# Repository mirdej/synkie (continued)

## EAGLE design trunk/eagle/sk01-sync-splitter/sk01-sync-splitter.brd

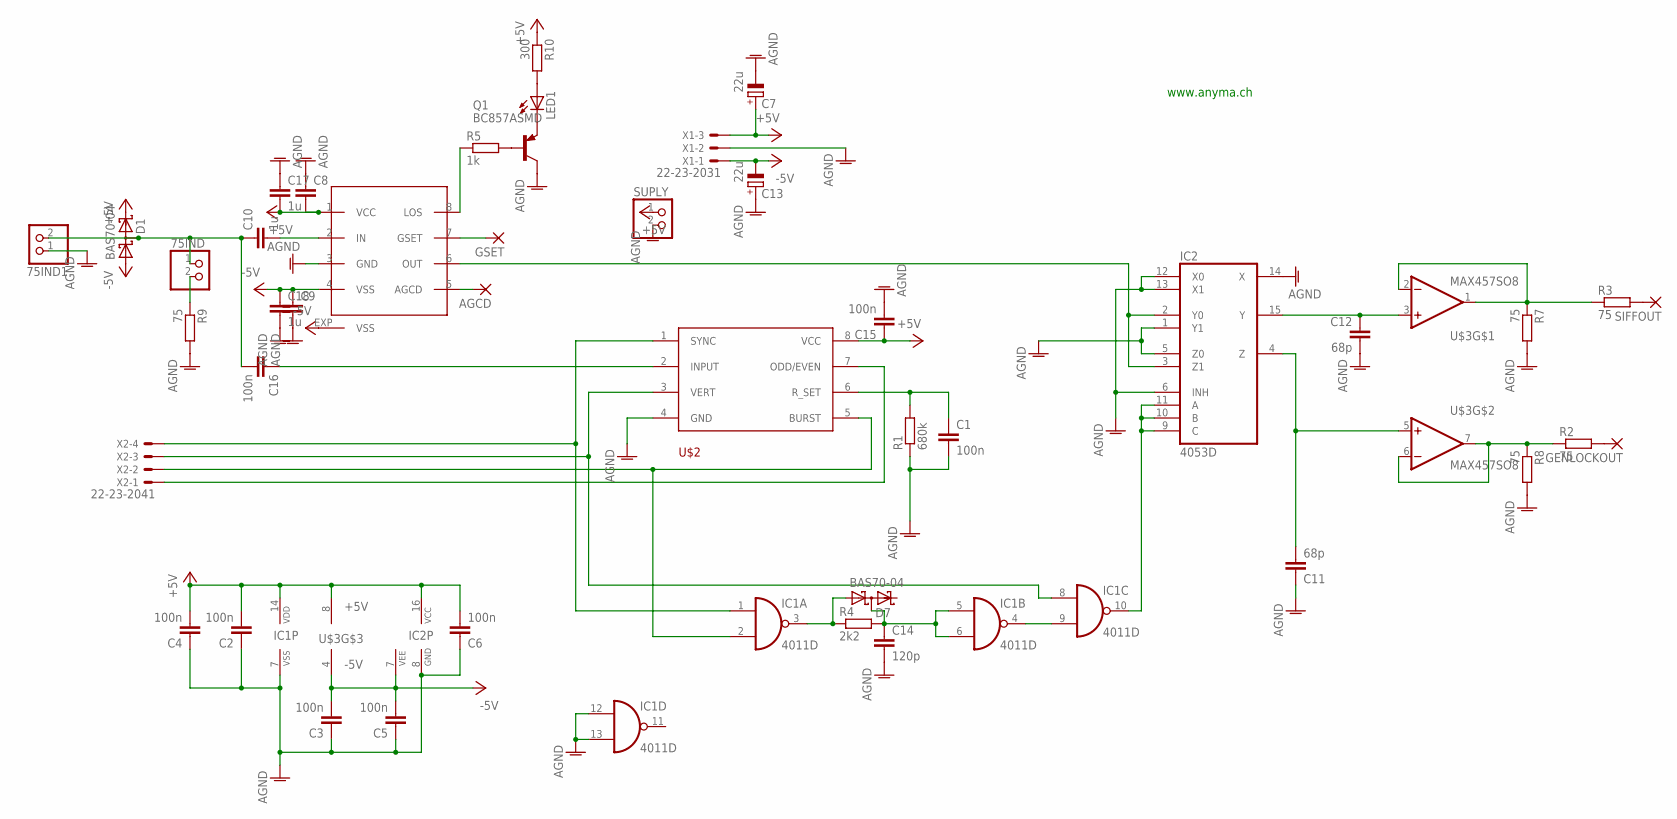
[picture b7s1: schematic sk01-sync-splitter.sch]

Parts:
75IND, 75IND1: PINHD-1X2; 1X02
AGCD: 3,17/1,1
C1, C2, C16: 100n; C1206
C3, C4, C5, C6, C15: 100n; C0805
C7, C13: 22u; CT3528
C8, C9: C-EUC0805; C0805
C10: 1u; C1206
C11, C12: 68p; C1206
C14: 120p; C1206
C17, C18: 1u; C0805
D1, D7: BAS70-04; SOT23
GENLOCKOUT: 3,17/1,1
GSET: 3,17/1,1
IC1: 4011D; SO14
IC2: 4053D; SO16
LED1: LED3MM
Q1: BC857ASMD; SOT23-BEC
R1: 680k; R1206
R2, R3, R7, R8, R9: 75; R1206
R4: 2k2; R1206
R5: 1k; R1206
R10: 300; R1206
SIFFOUT: 3,17/1,1
SUPLY: PINHD-1X2; 1X02
U$2: LM1881; SO08
U$3: MAX457SO8; SO08
U$4: MAX7450; SO08-EXP
X1: 22-23-2031
X2: 22-23-2041

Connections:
+5V: C2.2, C4.2, C6.2, C7.+, C8.2, C15.1, C17.2, D1.2 (C2), IC1.14 (VDD), IC2.16 (VCC), R10.1, SUPLY.1, U$2.8 (VCC), U$3.8 (+5V), U$4.1 (VCC), X1.3
-5V: C3.2, C5.2, C9.1, C13.-, C18.1, D1.1 (A1), IC2.7 (VEE), U$3.4 (-5V), U$4.4 (VSS), U$4.EXP (VSS), X1.1
AGND: 75IND1.1, C1.2, C2.1, C3.1, C4.1, C5.1, C6.1, C7.-, C8.1, C9.2, C11.1, C12.2, C13.+, C14.2, C15.2, C17.1, C18.2, IC1.7 (VSS), IC1.12 (I0), IC1.13 (I1), IC2.1 (Y1), IC2.5 (Z0), IC2.6 (INH), IC2.8 (GND), IC2.12 (X0), IC2.13 (X1), IC2.14 (X), Q1.C, R1.1, R7.2, R8.2, R9.2, SUPLY.2, U$2.4 (GND), U$4.3 (GND), X1.2
unnamed: IC1.1 (I0), U$2.1 (SYNC), X2.4
unnamed: LED1.A, R10.2
unnamed: IC1.2 (I1), U$2.5 (BURST), X2.2
unnamed: U$2.7 (ODD/EVEN), X2.1
unnamed: IC1.10 (O), IC2.9 (C), IC2.10 (B), IC2.11 (A)
unnamed: LED1.K (C), Q1.E
unnamed: C1.1, R1.2, U$2.6 (R_SET)
unnamed: Q1.B, R5.2
unnamed: 75IND.2, R9.1
unnamed: IC1.4 (O), IC1.9 (I1)
unnamed: C11.2, IC2.4 (Z), U$3.5 (+IN)
unnamed: C10.2, U$4.2 (IN)
unnamed: R3.2, SIFFOUT.1
unnamed: R2.1, R8.1, U$3.6 (-IN), U$3.7 (OUT)
unnamed: IC2.2 (Y0), IC2.3 (Z1), U$4.6 (OUT)
unnamed: R3.1, R7.1, U$3.1 (OUT), U$3.2 (-IN)
unnamed: C12.1, IC2.15 (Y), U$3.3 (+IN)
unnamed: IC1.8 (I0), U$2.3 (VERT), X2.3
unnamed: 75IND.1, 75IND1.2, C10.1, C16.2, D1.3 (C1A2)
unnamed: GSET.1, U$4.7 (GSET)
unnamed: C14.1, D7.3 (C1A2), IC1.5 (I0), IC1.6 (I1), R4.2
unnamed: GENLOCKOUT.1, R2.2
unnamed: D7.1 (A1), IC1.3 (O), R4.1
unnamed: R5.1, U$4.8 (LOS)
unnamed: C16.1, U$2.2 (INPUT)
unnamed: AGCD.1, U$4.5 (AGCD)

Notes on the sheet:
www.anyma.ch

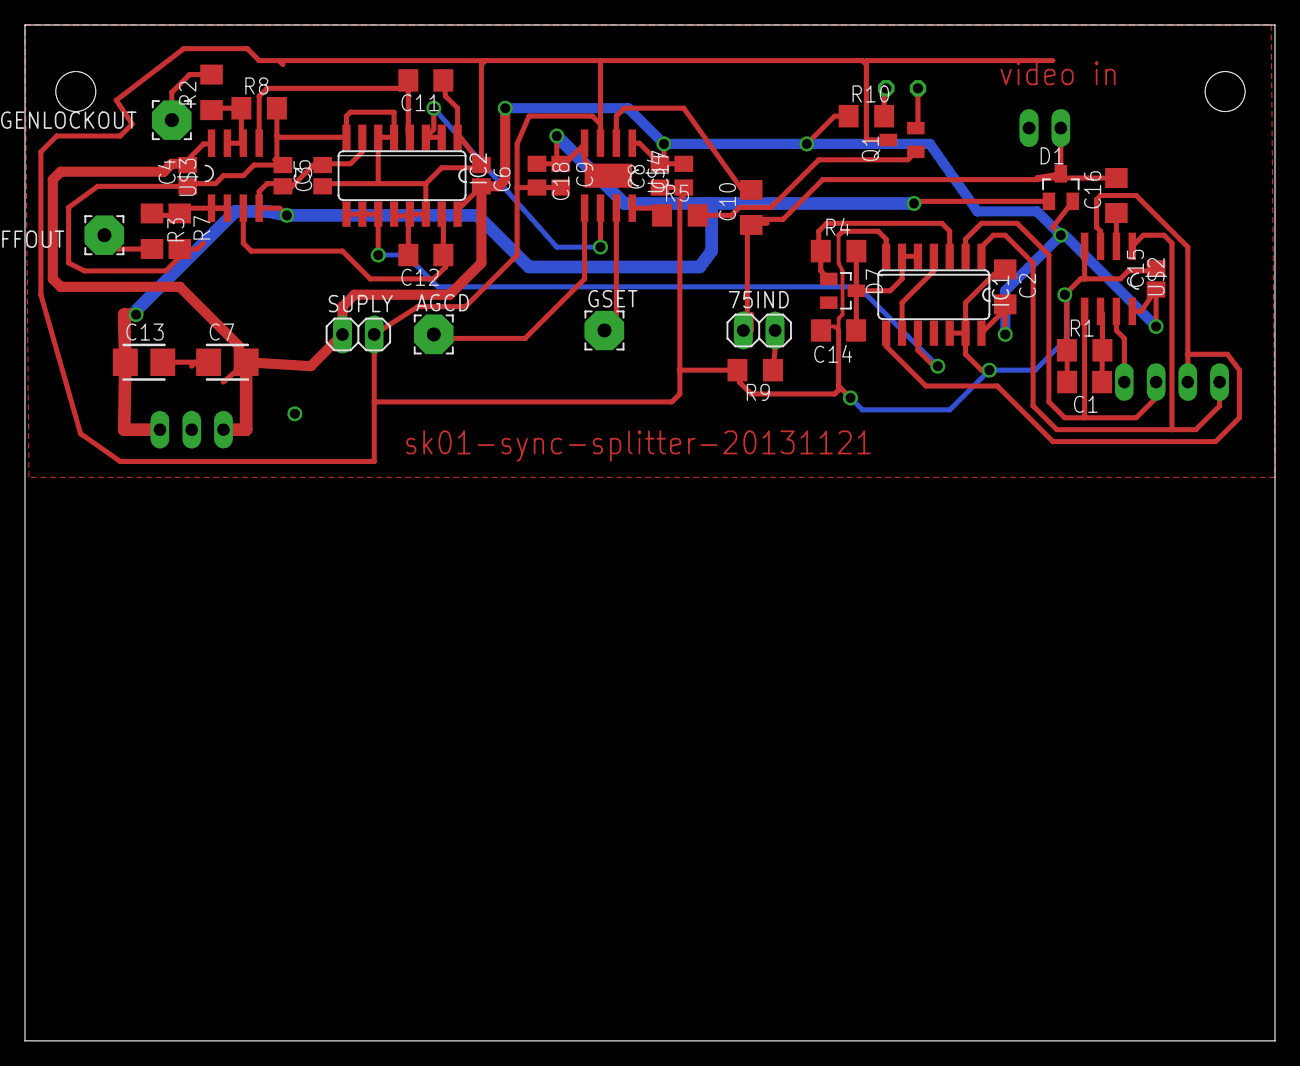
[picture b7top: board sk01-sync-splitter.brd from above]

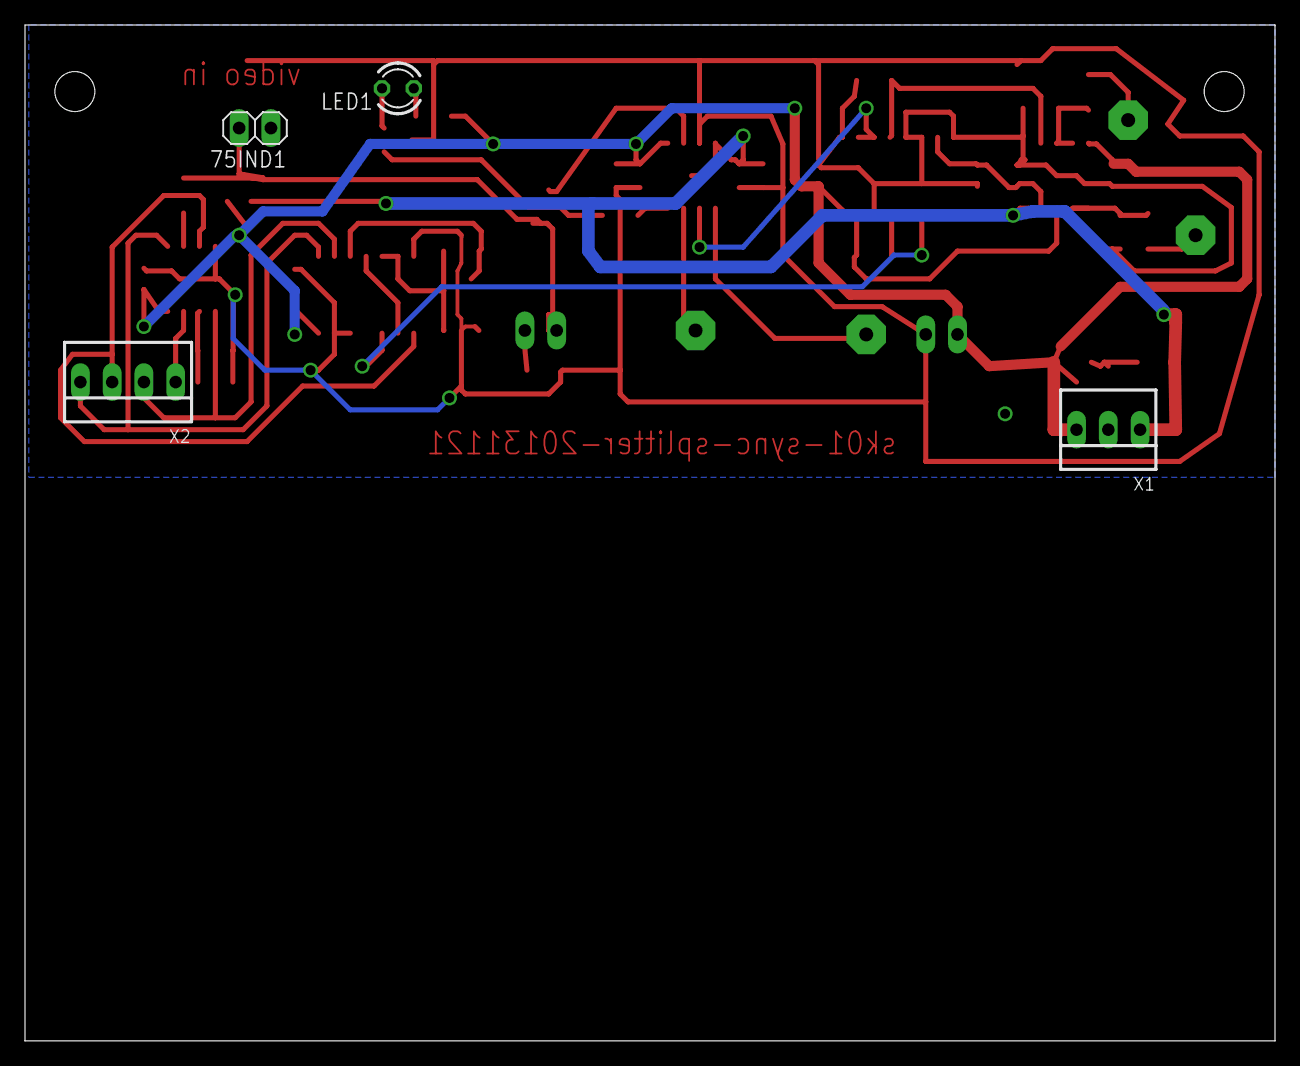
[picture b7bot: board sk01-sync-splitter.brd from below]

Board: 2 copper layers, 100.0 x 81.3 mm, 45 parts (4 on the bottom side), 29 nets.
